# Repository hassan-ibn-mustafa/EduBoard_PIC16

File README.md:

# EduBoard PIC16 - Trainer Kit

An educational, single-layer development board designed to simplify learning and prototyping with the Microchip PIC16F877A microcontroller. Designed entirely in KiCad, this board eliminates complexity and focuses on a modular, jumper-based routing architecture for students and electronics enthusiasts.

## 🔗 Live Interactive Preview
    
🌐 **[Click Here to View Live-Demo_&_Interactive_BOM & Project Website](https://hassan-ibn-mustafa.github.io/EduBoard_PIC16/)**

*Click the badge above to explore the live interactive web deployment and view the full layout directly in your browser!*

## 🗺️ Circuit Schematic

Here is the complete schematic diagram of the EduBoard PIC16. For a high-resolution scalable version, please check the `Docs/` directory.

<div align="center">
  
</div>

## 📸 3D Hardware Showcase

<div align="center">

</div>

## 📁 Repository Structure

The repository is organized to provide easy access to documentation, source files, and manufacturing data:

* **`Docs/`**: Contains easy-to-read PDF files for quick reference without needing CAD software.
  * `Schematic.pdf`
  * `Layout_Top.pdf`
  * `Layout_Bottom.pdf`
* **`Fabrication/`**: Contains the `.zip` file with standard Gerber and Drill files. This zip file is production-ready and can be directly uploaded to any PCB manufacturer (e.g., JLCPCB, PCBWay).
* **`images/`**: Contains 3D renders and physical photos of the board.

## ⚙️ Technical Specifications

* **Microcontroller:** Microchip PIC16F877A
* **PCB Details:** Single-Layer DIY-friendly design
* **EDA Tool:** KiCad
* **Display Peripherals:** 16x2 Character LCD & 4-digit 7-segment display (multiplexed via 74LS48).
* **Power Subsystem:** LM7805 voltage regulation via DC barrel jack.
* **Routing:** 100% jumper-wire configuration using precision female headers for maximum experimental flexibility.

## 🛠️ Fabrication & Manufacturing

To manufacture this board:
1. Navigate to the `Fabrication/` directory.
2. Download the provided `.zip` file.
3. Upload the `.zip` file directly to your preferred PCB manufacturer. No further CAM processing is required.

---
*Designed & Developed by **Hassan Mustafa Hashem** - Industrial Electronics & Control Engineering.*

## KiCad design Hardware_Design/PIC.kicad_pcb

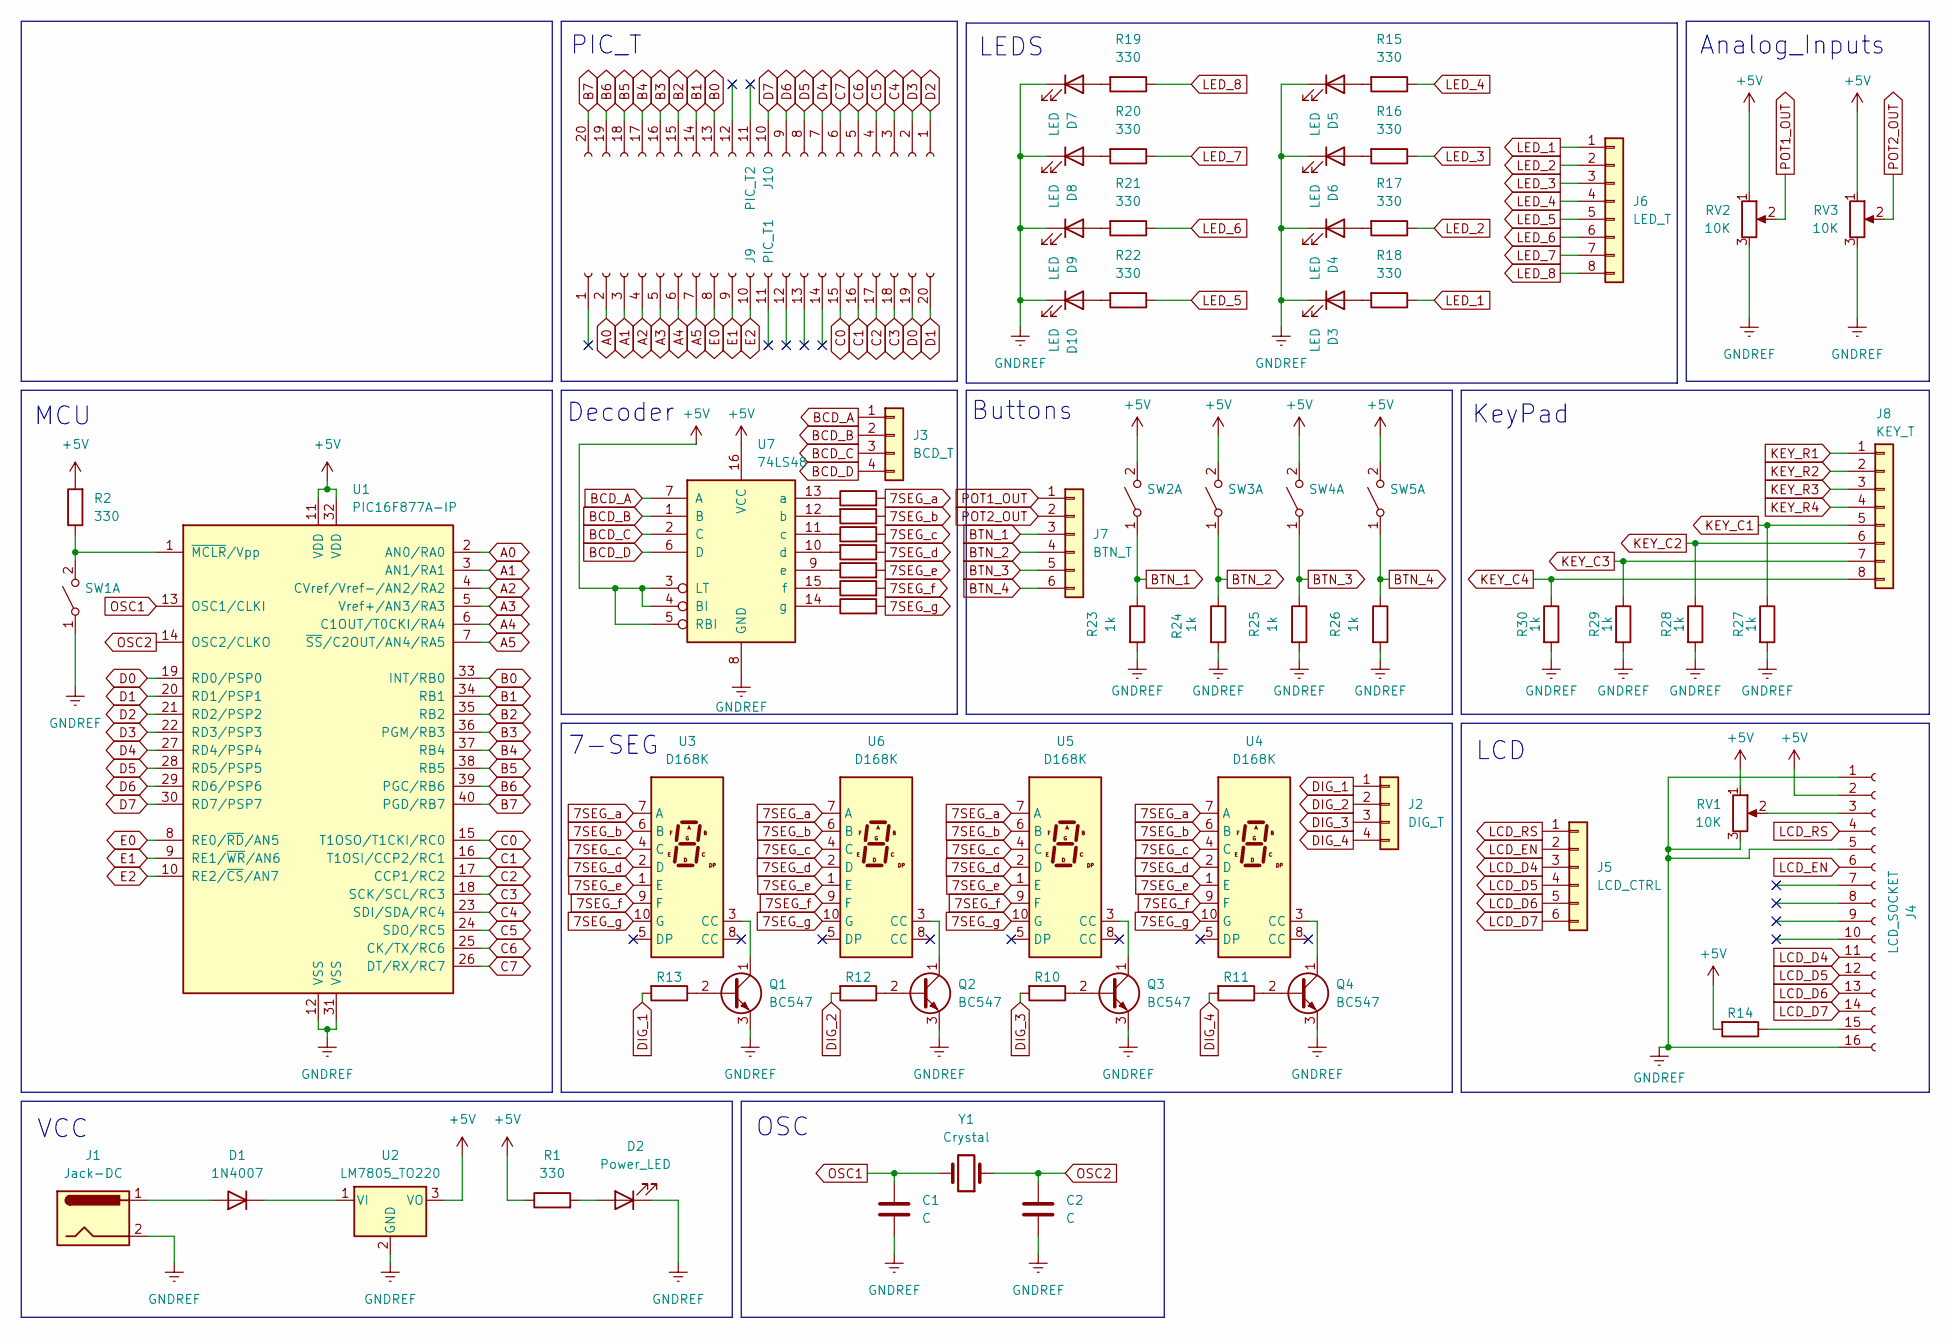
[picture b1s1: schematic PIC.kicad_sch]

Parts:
C1, C2: C; C_Disc_D5.0mm_W2.5mm_P5.00mm
D1: 1N4007; D_DO-41_SOD81_P10.16mm_Horizontal
D2: Power_LED; LED_D5.0mm
D3, D4, D5, D6, D7, D8, D9, D10: LED; LED_D5.0mm
J1: Jack-DC; BarrelJack_Horizontal
J2: DIG_T; PinSocket_1x04_P2.54mm_Vertical
J3: BCD_T; PinSocket_1x04_P2.54mm_Vertical
J4: LCD_SOCKET; PinSocket_1x16_P2.54mm_Vertical
J5: LCD_CTRL; PinSocket_1x06_P2.54mm_Vertical
J6: LED_T; PinSocket_1x08_P2.54mm_Vertical
J7: BTN_T; PinSocket_1x06_P2.54mm_Vertical
J8: KEY_T; PinSocket_1x08_P2.54mm_Vertical
J9: PIC_T1; PinSocket_1x20_P2.54mm_Vertical
J10: PIC_T2; PinSocket_1x20_P2.54mm_Vertical
Q1, Q2, Q3, Q4: BC547; TO-92_Inline
R1, R2, R3, R4, R5, R6, R7, R8, R9, R15, R16, R17, R18, R19, R20, R21, R22: 330; R_Axial_DIN0207_L6.3mm_D2.5mm_P7.62mm_Horizontal
R10, R11, R12, R13, R14: 1K; R_Axial_DIN0207_L6.3mm_D2.5mm_P7.62mm_Horizontal
R23, R24, R25, R26, R27, R28, R29, R30: 1k; R_Axial_DIN0207_L6.3mm_D2.5mm_P7.62mm_Horizontal
RV1, RV2, RV3: 10K; Potentiometer_Alps_RK163_Single_Horizontal
SW1, SW2, SW3, SW4, SW5: SW_DPST_x2; SW_PUSH_6mm
U1: PIC16F877A-IP; DIP-40_W15.24mm
U2: LM7805_TO220; TO-220-3_Vertical
U3, U4, U5, U6: D168K; D1X8K
U7: 74LS48; DIP-16_W7.62mm
Y1: Crystal; Crystal_HC49-4H_Vertical

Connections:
7SEG_a: R3.2, U3.7 (A), U4.7 (A), U5.7 (A), U6.7 (A)
7SEG_b: R4.1, U3.6 (B), U4.6 (B), U5.6 (B), U6.6 (B)
7SEG_c: R5.2, U3.4 (C), U4.4 (C), U5.4 (C), U6.4 (C)
7SEG_d: R6.1, U3.2 (D), U4.2 (D), U5.2 (D), U6.2 (D)
7SEG_e: R7.2, U3.1 (E), U4.1 (E), U5.1 (E), U6.1 (E)
7SEG_f: R8.2, U3.9 (F), U4.9 (F), U5.9 (F), U6.9 (F)
7SEG_g: R9.2, U3.10 (G), U4.10 (G), U5.10 (G), U6.10 (G)
+5V: J4.2, R1.1, R2.2, R14.2, RV1.1, RV2.1, RV3.1, SW2.2 (B), SW3.2 (B), SW4.2 (B), SW5.2 (B), U1.11 (VDD), U1.32 (VDD), U2.3 (VO), U7.3 (LT), U7.4 (BI), U7.5 (RBI), U7.16 (VCC)
A0: J9.2, U1.2 (AN0/RA0)
A1: J9.3, U1.3 (AN1/RA1)
A2: J9.4, U1.4 (CVref/Vref-/AN2/RA2)
A3: J9.5, U1.5 (Vref+/AN3/RA3)
A4: J9.6, U1.6 (C1OUT/T0CKI/RA4)
A5: J9.7, U1.7 (~SS/C2OUT/AN4/RA5)
B0: J10.13, U1.33 (INT/RB0)
B1: J10.14, U1.34 (RB1)
B2: J10.15, U1.35 (RB2)
B3: J10.16, U1.36 (PGM/RB3)
B4: J10.17, U1.37 (RB4)
B5: J10.18, U1.38 (RB5)
B6: J10.19, U1.39 (PGC/RB6)
B7: J10.20, U1.40 (PGD/RB7)
BCD_A: J3.1, U7.7 (A)
BCD_B: J3.2, U7.1 (B)
BCD_C: J3.3, U7.2 (C)
BCD_D: J3.4, U7.6 (D)
BTN_1: J7.3, R23.1, SW2.1 (A)
BTN_2: J7.4, R24.1, SW3.1 (A)
BTN_3: J7.5, R25.1, SW4.1 (A)
BTN_4: J7.6, R26.1, SW5.1 (A)
C0: J9.15, U1.15 (T1OSO/T1CKI/RC0)
C1: J9.16, U1.16 (T1OSI/CCP2/RC1)
C2: J9.17, U1.17 (CCP1/RC2)
C3: J9.18, U1.18 (SCK/SCL/RC3)
C4: J10.3, U1.23 (SDI/SDA/RC4)
C5: J10.4, U1.24 (SDO/RC5)
C6: J10.5, U1.25 (CK/TX/RC6)
C7: J10.6, U1.26 (DT/RX/RC7)
D0: J9.19, U1.19 (RD0/PSP0)
D1: J9.20, U1.20 (RD1/PSP1)
D2: J10.1, U1.21 (RD2/PSP2)
D3: J10.2, U1.22 (RD3/PSP3)
D4: J10.7, U1.27 (RD4/PSP4)
D5: J10.8, U1.28 (RD5/PSP5)
D6: J10.9, U1.29 (RD6/PSP6)
D7: J10.10, U1.30 (RD7/PSP7)
DIG_1: J2.1, R13.2
DIG_2: J2.2, R12.2
DIG_3: J2.3, R10.2
DIG_4: J2.4, R11.2
E0: J9.8, U1.8 (RE0/~RD/AN5)
E1: J9.9, U1.9 (RE1/~WR/AN6)
E2: J9.10, U1.10 (RE2/~CS/AN7)
GNDREF: C1.2, C2.2, D2.1 (K), D3.1 (K), D4.1 (K), D5.1 (K), D6.1 (K), D7.1 (K), D8.1 (K), D9.1 (K), D10.1 (K), J1.2, J4.1, J4.5, J4.16, Q1.3 (E), Q2.3 (E), Q3.3 (E), Q4.3 (E), R23.2, R24.2, R25.2, R26.2, R27.2, R28.2, R29.2, R30.2, RV1.3, RV2.3, RV3.3, SW1.1 (A), U1.12 (VSS), U1.31 (VSS), U2.2 (GND), U7.8 (GND)
KEY_C1: J8.5, R27.1
KEY_C2: J8.6, R28.1
KEY_C3: J8.7, R29.1
KEY_C4: J8.8, R30.1
KEY_R1: J8.1
KEY_R2: J8.2
KEY_R3: J8.3
KEY_R4: J8.4
LCD_D4: J4.11, J5.3
LCD_D5: J4.12, J5.4
LCD_D6: J4.13, J5.5
LCD_D7: J4.14, J5.6
LCD_EN: J4.6, J5.2
LCD_RS: J4.4, J5.1
LED_1: J6.1, R18.1
LED_2: J6.2, R17.1
LED_3: J6.3, R16.1
LED_4: J6.4, R15.1
LED_5: J6.5, R22.1
LED_6: J6.6, R21.1
LED_7: J6.7, R20.1
LED_8: J6.8, R19.1
unnamed: D1.2 (A), J1.1
unnamed: D1.1 (K), U2.1 (VI)
unnamed: D2.2 (A), R1.2
unnamed: D3.2 (A), R18.2
unnamed: D4.2 (A), R17.2
unnamed: D5.2 (A), R15.2
unnamed: D6.2 (A), R16.2
unnamed: D7.2 (A), R19.2
unnamed: D8.2 (A), R20.2
unnamed: D9.2 (A), R21.2
unnamed: D10.2 (A), R22.2
unnamed: J4.3, RV1.2
unnamed: J4.15, R14.1
unnamed: Q1.2 (B), R13.1
unnamed: Q1.1 (C), U3.3 (CC)
unnamed: Q2.2 (B), R12.1
unnamed: Q2.1 (C), U6.3 (CC)
unnamed: Q3.2 (B), R10.1
unnamed: Q3.1 (C), U5.3 (CC)
unnamed: Q4.2 (B), R11.1
unnamed: Q4.1 (C), U4.3 (CC)
unnamed: R2.1, SW1.2 (B), U1.1 (~MCLR/Vpp)
unnamed: R3.1, U7.13 (a)
unnamed: R4.2, U7.12 (b)
unnamed: R5.1, U7.11 (c)
unnamed: R6.2, U7.10 (d)
unnamed: R7.1, U7.9 (e)
unnamed: R8.1, U7.15 (f)
unnamed: R9.1, U7.14 (g)
OSC1: C1.1, U1.13 (OSC1/CLKI), Y1.2
OSC2: C2.1, U1.14 (OSC2/CLKO), Y1.1
POT1_OUT: J7.1, RV2.2
POT2_OUT: J7.2, RV3.2

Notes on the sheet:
Analog_Inputs
Buttons
LCD
KeyPad
LEDS
PIC_T
OSC
VCC
7-SEG
Decoder
MCU

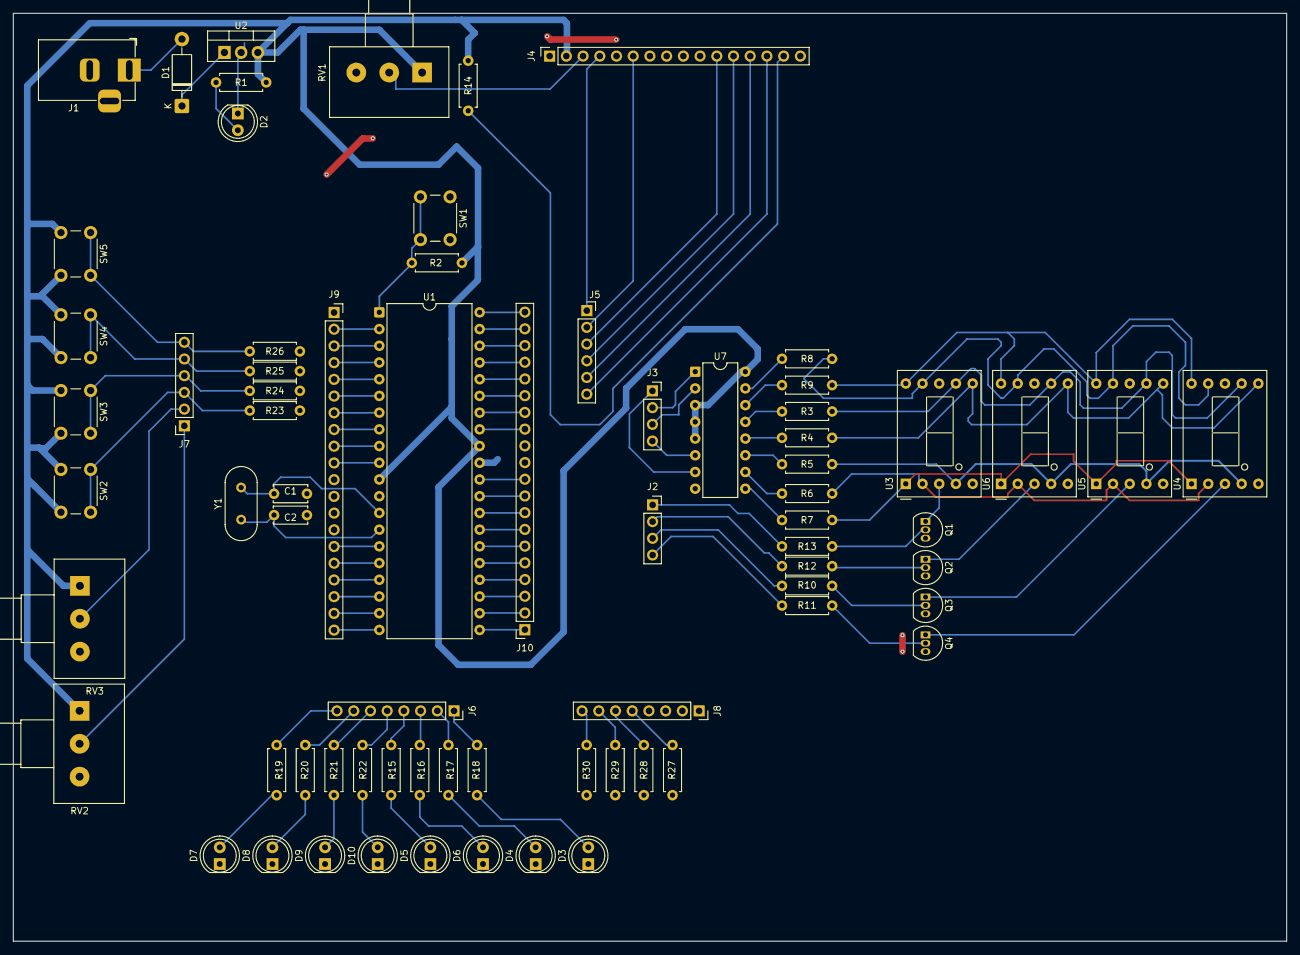
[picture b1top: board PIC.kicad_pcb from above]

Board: 2 copper layers, 193.5 x 141.0 mm, 72 parts (0 on the bottom side), 105 nets.

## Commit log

2026-05-24 adding Fabrication files & images for the project
2026-05-24 Correct image source path for PCB Top View
    Fix image source formatting in README.md
2026-05-24 Fix image path for schematic diagram in README
2026-05-24 Add live interactive preview section to README
    Added a section for live interactive preview with a link to the demo and project website.
2026-05-25 Change project website link to EduBoard_PIC16
    Updated the project website link in the README.
